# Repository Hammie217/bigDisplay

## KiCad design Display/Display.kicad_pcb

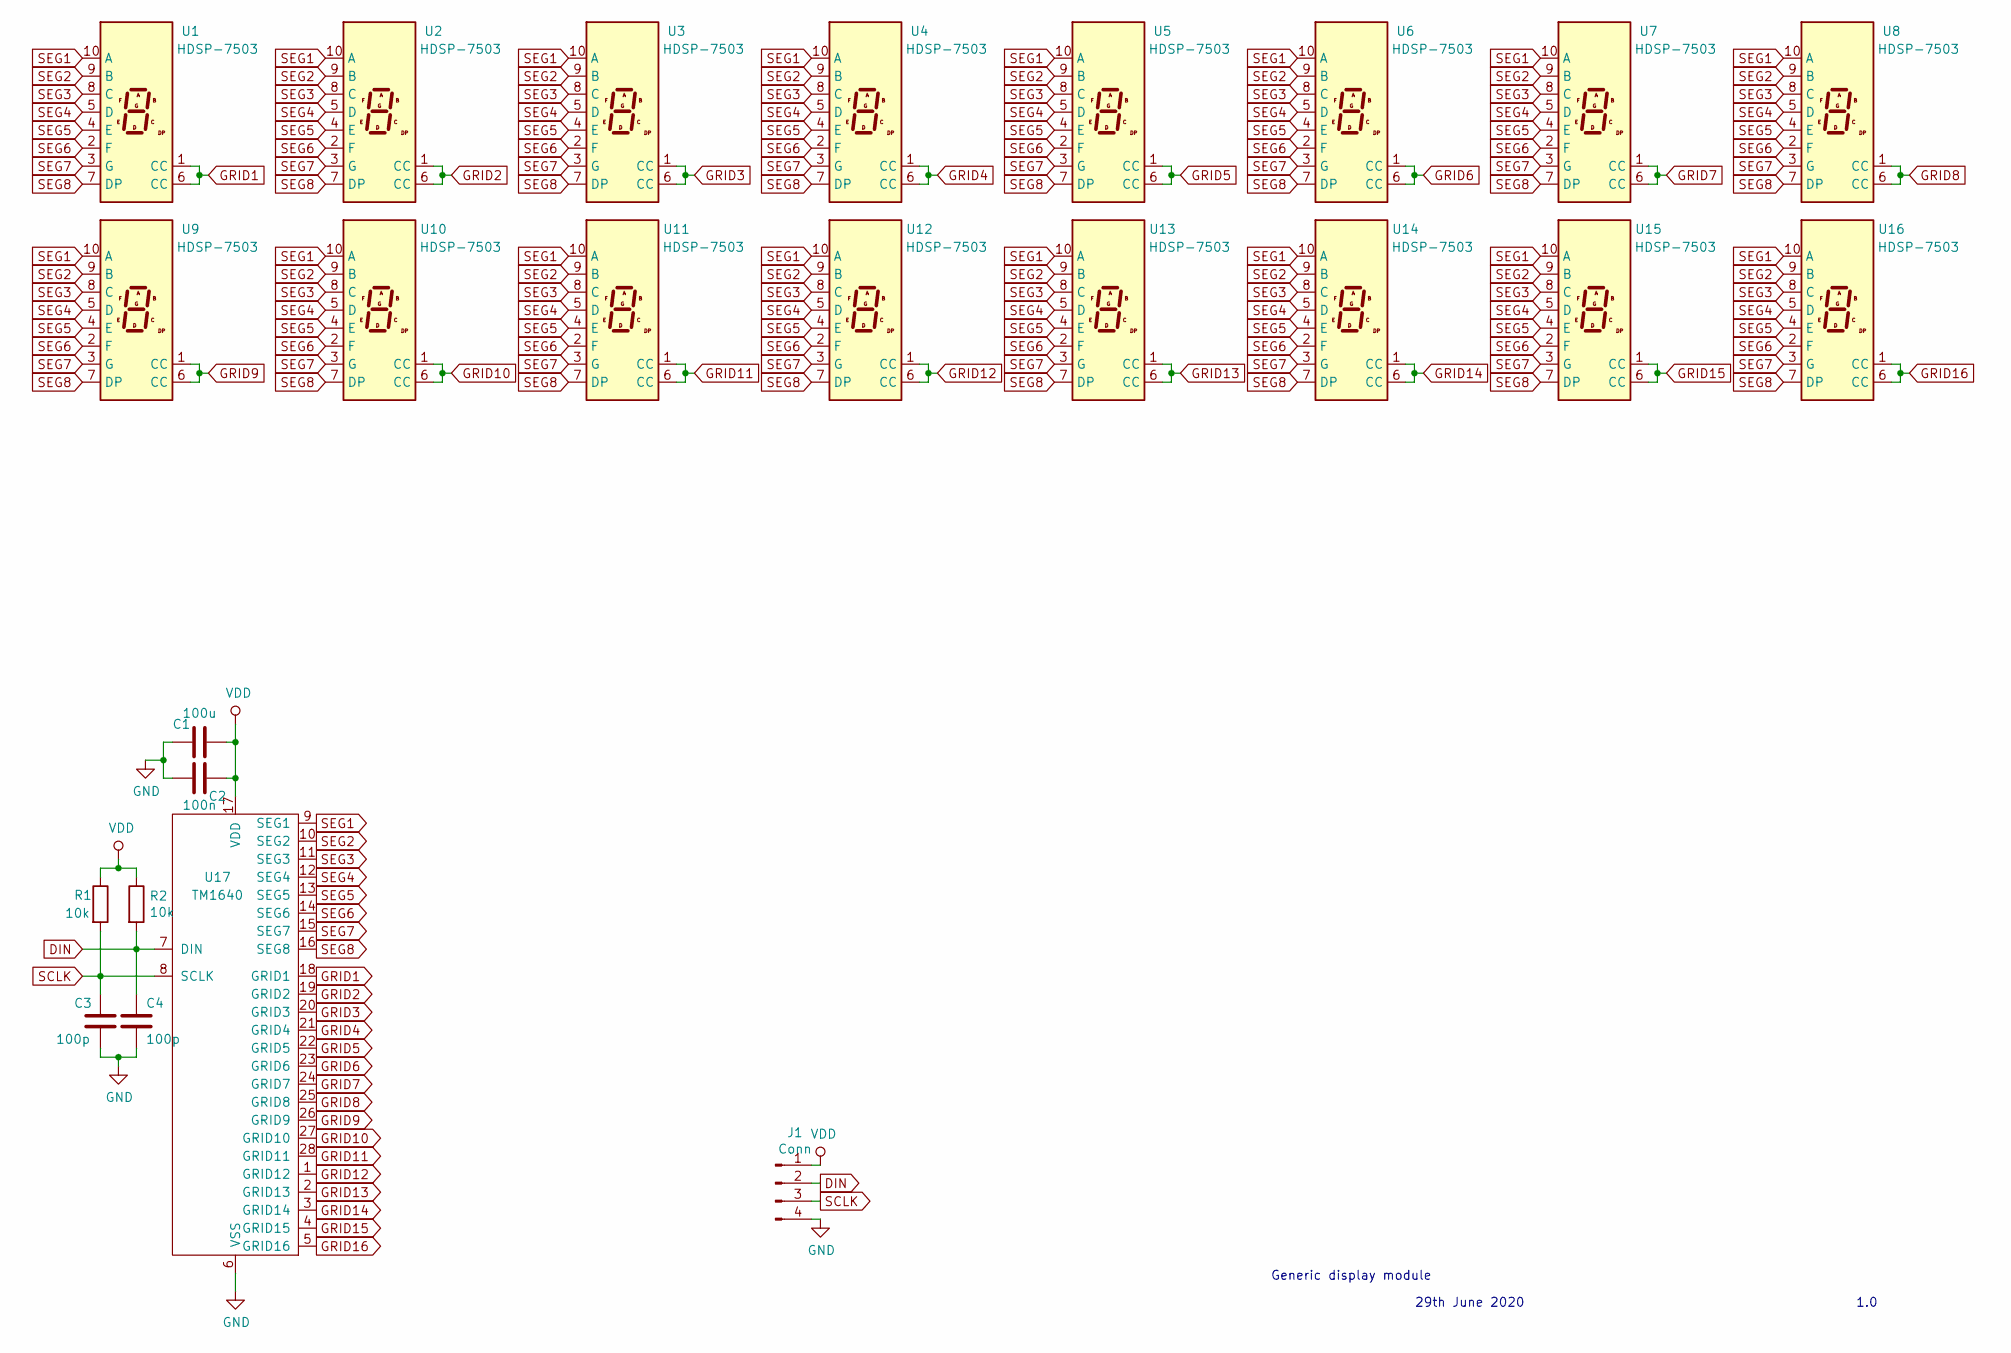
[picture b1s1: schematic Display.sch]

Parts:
C1: 100u; CP_EIA-3528-12_Kemet-T
C2: 100n; C_0603_1608Metric
C3, C4: 100p; C_0603_1608Metric
J1: Conn; PinHeader_1x04_P2.54mm_Vertical
R1, R2: 10k; R_0603_1608Metric
U1, U2, U3, U4, U5, U6, U7, U8, U9, U10, U11, U12, U13, U14, U15, U16: HDSP-7503; HDSP-A151
U17: TM1640; SOIC-28

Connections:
DIN: C4.1, J1.2, R2.2, U17.7 (DIN)
GND: C1.2, C2.1, C3.2, C4.2, J1.4, U17.6 (VSS)
GRID1: U1.1 (CC), U1.6 (CC), U17.18 (GRID1)
GRID2: U2.1 (CC), U2.6 (CC), U17.19 (GRID2)
GRID3: U3.1 (CC), U3.6 (CC), U17.20 (GRID3)
GRID4: U4.1 (CC), U4.6 (CC), U17.21 (GRID4)
GRID5: U5.1 (CC), U5.6 (CC), U17.22 (GRID5)
GRID6: U6.1 (CC), U6.6 (CC), U17.23 (GRID6)
GRID7: U7.1 (CC), U7.6 (CC), U17.24 (GRID7)
GRID8: U8.1 (CC), U8.6 (CC), U17.25 (GRID8)
GRID9: U9.1 (CC), U9.6 (CC), U17.26 (GRID9)
GRID10: U10.1 (CC), U10.6 (CC), U17.27 (GRID10)
GRID11: U11.1 (CC), U11.6 (CC), U17.28 (GRID11)
GRID12: U12.1 (CC), U12.6 (CC), U17.1 (GRID12)
GRID13: U13.1 (CC), U13.6 (CC), U17.2 (GRID13)
GRID14: U14.1 (CC), U14.6 (CC), U17.3 (GRID14)
GRID15: U15.1 (CC), U15.6 (CC), U17.4 (GRID15)
GRID16: U16.1 (CC), U16.6 (CC), U17.5 (GRID16)
SCLK: C3.1, J1.3, R1.2, U17.8 (SCLK)
SEG1: U1.10 (A), U2.10 (A), U3.10 (A), U4.10 (A), U5.10 (A), U6.10 (A), U7.10 (A), U8.10 (A), U9.10 (A), U10.10 (A), U11.10 (A), U12.10 (A), U13.10 (A), U14.10 (A), U15.10 (A), U16.10 (A), U17.9 (SEG1)
SEG2: U1.9 (B), U2.9 (B), U3.9 (B), U4.9 (B), U5.9 (B), U6.9 (B), U7.9 (B), U8.9 (B), U9.9 (B), U10.9 (B), U11.9 (B), U12.9 (B), U13.9 (B), U14.9 (B), U15.9 (B), U16.9 (B), U17.10 (SEG2)
SEG3: U1.8 (C), U2.8 (C), U3.8 (C), U4.8 (C), U5.8 (C), U6.8 (C), U7.8 (C), U8.8 (C), U9.8 (C), U10.8 (C), U11.8 (C), U12.8 (C), U13.8 (C), U14.8 (C), U15.8 (C), U16.8 (C), U17.11 (SEG3)
SEG4: U1.5 (D), U2.5 (D), U3.5 (D), U4.5 (D), U5.5 (D), U6.5 (D), U7.5 (D), U8.5 (D), U9.5 (D), U10.5 (D), U11.5 (D), U12.5 (D), U13.5 (D), U14.5 (D), U15.5 (D), U16.5 (D), U17.12 (SEG4)
SEG5: U1.4 (E), U2.4 (E), U3.4 (E), U4.4 (E), U5.4 (E), U6.4 (E), U7.4 (E), U8.4 (E), U9.4 (E), U10.4 (E), U11.4 (E), U12.4 (E), U13.4 (E), U14.4 (E), U15.4 (E), U16.4 (E), U17.13 (SEG5)
SEG6: U1.2 (F), U2.2 (F), U3.2 (F), U4.2 (F), U5.2 (F), U6.2 (F), U7.2 (F), U8.2 (F), U9.2 (F), U10.2 (F), U11.2 (F), U12.2 (F), U13.2 (F), U14.2 (F), U15.2 (F), U16.2 (F), U17.14 (SEG6)
SEG7: U1.3 (G), U2.3 (G), U3.3 (G), U4.3 (G), U5.3 (G), U6.3 (G), U7.3 (G), U8.3 (G), U9.3 (G), U10.3 (G), U11.3 (G), U12.3 (G), U13.3 (G), U14.3 (G), U15.3 (G), U16.3 (G), U17.15 (SEG7)
SEG8: U1.7 (DP), U2.7 (DP), U3.7 (DP), U4.7 (DP), U5.7 (DP), U6.7 (DP), U7.7 (DP), U8.7 (DP), U9.7 (DP), U10.7 (DP), U11.7 (DP), U12.7 (DP), U13.7 (DP), U14.7 (DP), U15.7 (DP), U16.7 (DP), U17.16 (SEG8)
VDD: C1.1, C2.2, J1.1, R1.1, R2.1, U17.17 (VDD)

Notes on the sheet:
Generic display module
29th June 2020
1.0

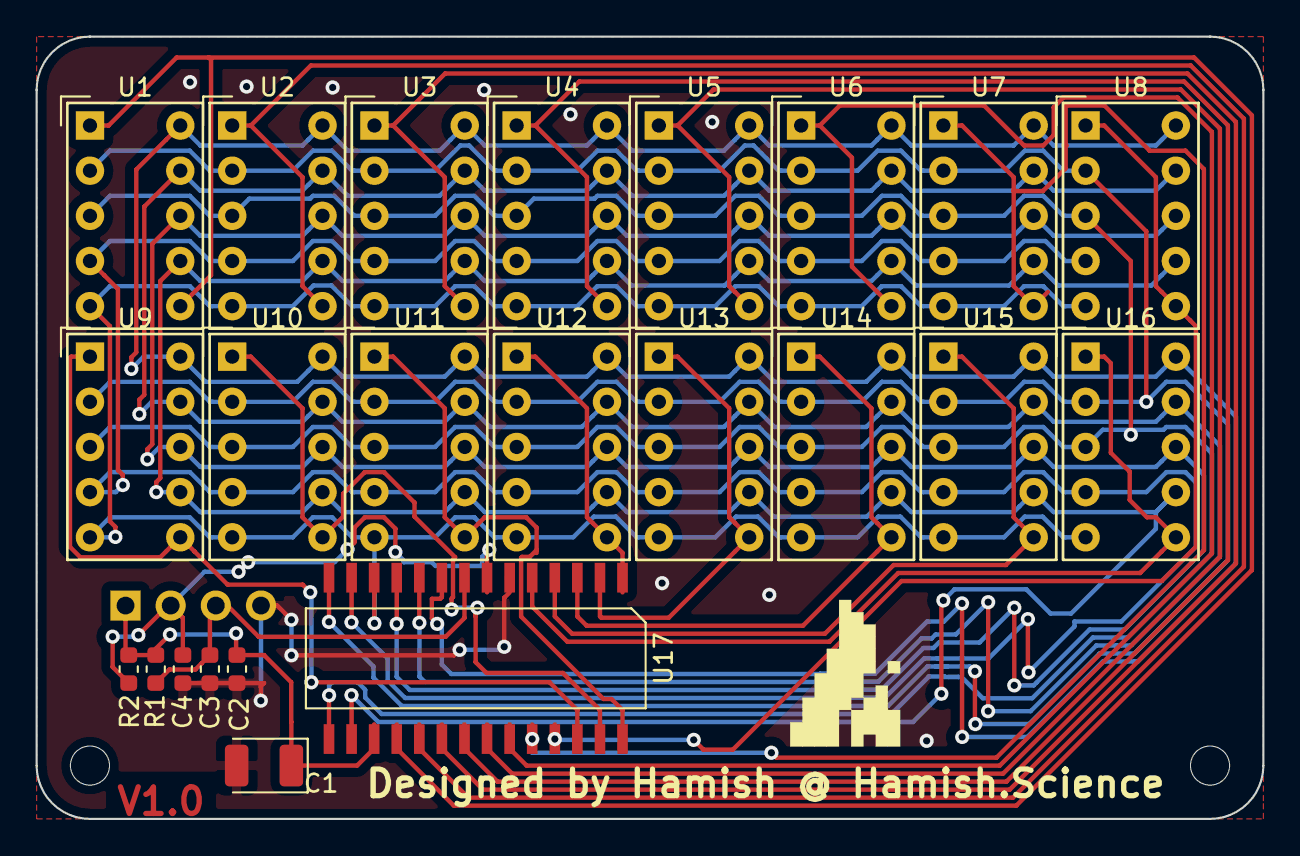
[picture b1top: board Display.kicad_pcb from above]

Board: 2 copper layers, 69.0 x 44.0 mm, 25 parts (1 on the bottom side), 28 nets.

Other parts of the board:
LOGO: LOGO

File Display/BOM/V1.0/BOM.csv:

Reference, Quantity, Value, Footprint, Datasheet
C1,1,100u,CP_EIA-3528-12_Kemet-T,~
C2,1,100n,Capacitor_SMD:C_0603_1608Metric,~
C4 C3,2,100p,Capacitor_SMD:C_0603_1608Metric,~
J1,1,Conn,Connector_PinHeader_2.54mm:PinHeader_1x04_P2.54mm_Vertical,~
R2 R1,2,10k,Resistor_SMD:R_0603_1608Metric,~
U1 U2 U3 U4 U5 U6 U7 U8 U9 U10 U11 U12 U13 U14 U15 U16,16,HDSP-7503,Display_7Segment:HDSP-A151,https://docs.broadcom.com/docs/AV02-2553EN
U17,1,TM1640,Symbol:SOIC-28,
